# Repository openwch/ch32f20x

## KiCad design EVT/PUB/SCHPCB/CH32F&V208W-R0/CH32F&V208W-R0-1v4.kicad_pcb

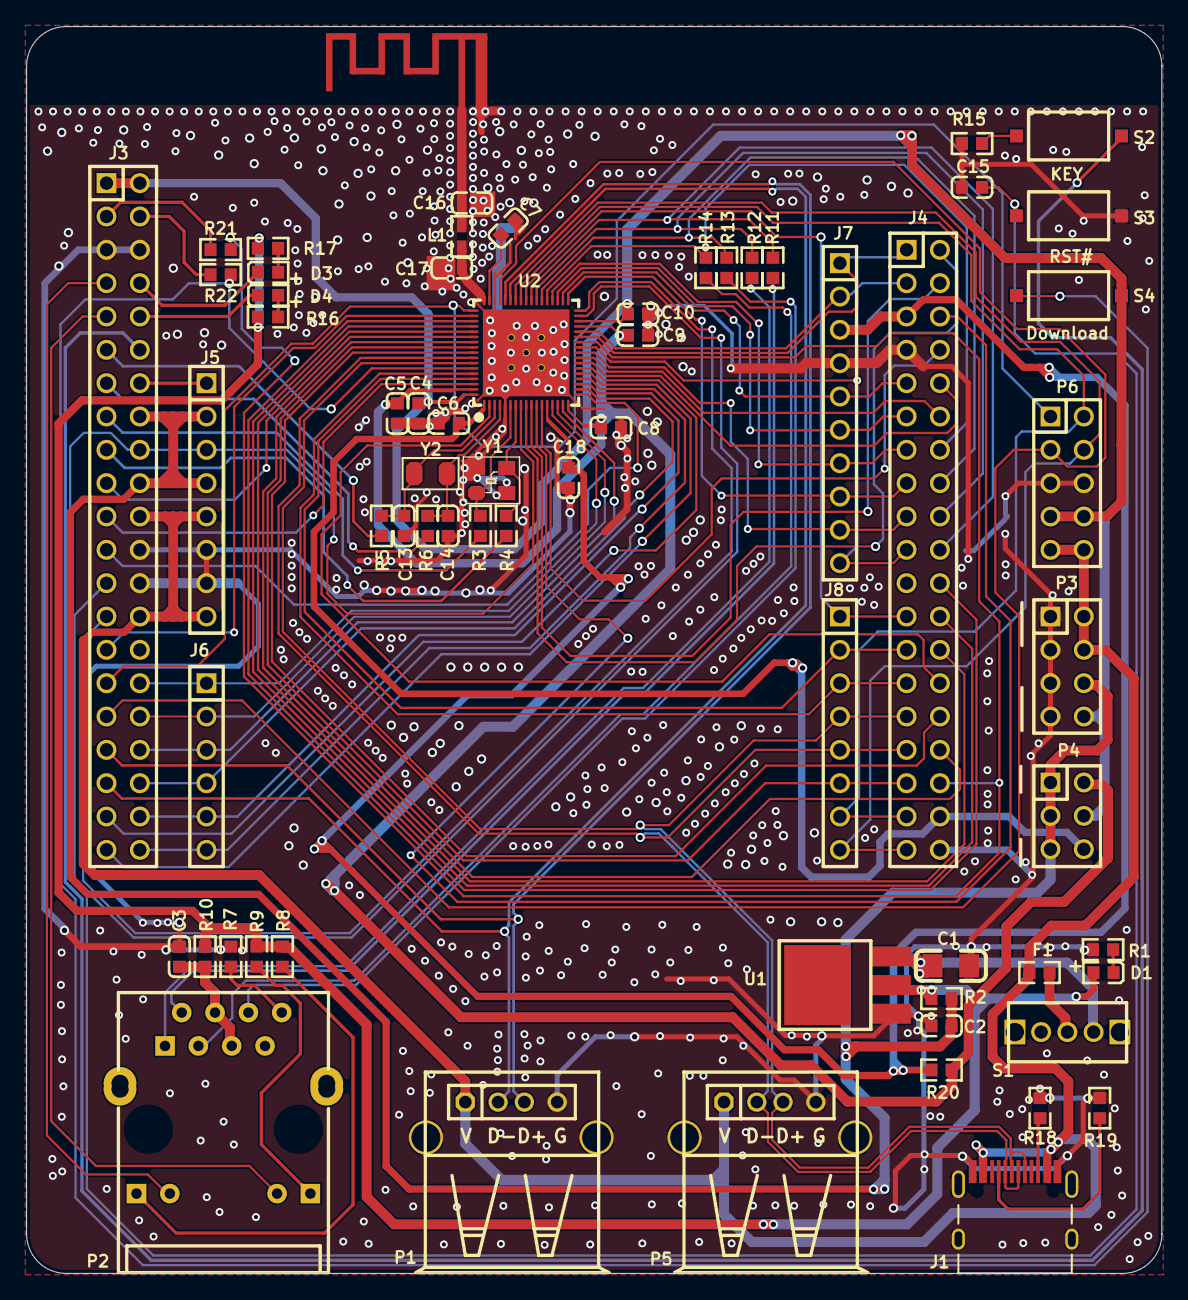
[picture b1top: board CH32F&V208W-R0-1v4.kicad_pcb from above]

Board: 2 copper layers, 86.5 x 95.0 mm, 65 parts (0 on the bottom side), 96 nets.

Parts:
C1: 10uF; 3216_C
C2: 10uF; 0603_C
C3, C4, C5, C6, C8, C9, C10, C15, C18: 0.1uF; 0603_C
C7: 1uF; 0603_C
C13, C14: 12pF; 0603_C
C16: 1.5pF; 0603_C
C17: 1pF; 0603_C
D1: power; 0603+
D3, D4: RED; 0603+
E1: ANTENNA; ANT-F-1-2.4G-1.6
F1: 500mA; 0603
J1: TYPE-C-Receptacle-2.0
J3: Header 21X2; IDC42-2.54mm
J4: Header 19X2; IDC38-2.54mm
J5, J8: Header 8; SIP8-2.54mm
J6: Header 6; SIP6-2.54MM
J7: Header 10; SIP10-2.54mm
L1: 1.8nH; 0603
P1, P5: USB; USBAF
P2: HR911105A
P3: HEADER 4x2; IDC8-2.54mm
P4: Psel; IDC6-2.54mm
P6: LINK; IDC10-2.54mm
R1, R8, R9, R16, R17: 1K; 0603
R2, R7, R10, R20: 0Ω; 0603
R3, R4, R5, R6, R11, R12, R13, R14: NC(0R); 0603
R15, R21, R22: 10K; 0603
R18, R19: NC(5.1K); 0603
S1: SW SPDT; KEY_B
S2: KEY; SMD_6.1x3.65x2.5mm-KEY
S3: RST#; SMD_6.1x3.65x2.5mm-KEY
S4: Download; SMD_6.1x3.65x2.5mm-KEY
U1: 1117-3.3V; SOT-223
U2: CH32F208W; QFN68_8x8
Y1: 32MHz; XT3225
Y2: 32768Hz; FC-135

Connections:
3V3: C2.1, J3.16, J3.20, J5.2, J5.4, P3.6, P4.1, P4.3, P4.5, R2.1
3V3S: D1.1, R2.2, R8.1, R9.1, R10.2, R16.1, R17.1, U1.2
+5V: F1.1, J1.A4, J1.B4, J3.22, J3.28, J5.5, J5.8, P1.1, P3.2, P3.4, P5.1, P6.9, P6.10
ANT: C17.2, L1.1, U2.51
BOOT0: R22.2, S4.2, U2.63
BOOT1: J4.34, R21.1, U2.28
CC1: J1.A5, R19.1
CC2: J1.B5, R18.1
ELED1: J3.7, P2.10
ELED2: J3.9, P2.11
ERXN: P2.6, R13.2
ERXP: P2.3, R14.2
ETXN: P2.2, R11.2
ETXP: P2.1, R12.2
GND: C1.2, C2.2, C3.1, C4.2, C5.1, C6.2, C7.2, C8.2, C9.2, C10.1, C13.1, C14.1, C15.1, C16.1, C17.1, C18.2, E1.0, J1.0, J1.A1, J1.B1, J3.5, J3.6, J3.24, J3.26, J4.7, J4.38, J5.6, J5.7, J7.4, P1.0, P1.4, P3.1, P3.3, P3.5, P3.7, P5.0, P5.4, P6.5, P6.6, R1.1, R7.1, R15.1, R18.2, R19.2, S3.1, U1.1, U2.0, U2.5, U2.49, Y1.2, Y1.4
KEY: J3.12, S2.1
LED1: D3.2, J3.8
LED2: D4.2, J3.10
NRST: C15.2, J3.18, J5.3, S3.2, U2.8
NetC3_2: C3.2, P2.4, P2.5, R10.1
NetC16_2: C16.2, E1.1, L1.2
NetD1_2: D1.2, R1.2
NetD3_1: D3.1, R17.2
NetD4_1: D4.1, R16.2
NetF1_2: F1.2, S1.1
NetJ3_3: J3.3, R21.2
NetJ3_4: J3.4, R22.1
NetJ3_14: J3.14, J5.1
NetP2_8: P2.8, R7.2
NetP2_9: P2.9, R8.2
NetP2_12: P2.12, R9.2
NetR15_2: R15.2, S2.2
PA0: J3.32, J6.1, U2.14
PA1: J3.34, J6.2, U2.15
PA2: J3.36, J6.3, U2.16
PA3: J3.38, J6.4, U2.19
PA4: J3.40, J6.5, U2.20
PA5: J3.42, J6.6, U2.21
PA6: J3.41, U2.22
PA7: J3.39, U2.23
PA8: J4.23, J8.1, U2.43
PA9: J4.35, J8.7, P6.2, U2.44
PA10: J4.37, J8.8, P6.4, U2.45
PA11: J3.37, P1.2, U2.46
PA12: J3.35, P1.3, U2.47
PA13: J3.33, P6.3, U2.48
PA14: J3.31, P6.1, U2.52
PA15: J3.29, U2.53
PB0: J4.17, J7.9, U2.26
PB1: J4.19, J7.10, U2.27
PB3: J4.32, U2.58
PB4: J4.33, J8.6, U2.59
PB5: J4.30, U2.60
PB6: J1.A7, J1.B7, J4.31, J8.5, P5.2, U2.61
PB7: J1.A6, J1.B6, J4.29, J8.4, P5.3, U2.62
PB8: J4.27, J8.3, U2.64
PB9: J4.25, J8.2, U2.65
PB10: J4.1, J7.1, U2.29
PB11: J4.3, J7.2, U2.30
PB12: J4.15, J7.8, U2.35
PB13: J4.9, J7.5, U2.36
PB14: J4.11, J7.6, U2.37
PB15: J4.13, J7.7, U2.38
PC0: J4.2, U2.9
PC1: J4.4, U2.10
PC2: J4.6, U2.11
PC3: J4.8, U2.12
PC4: J4.10, U2.24
PC5: J4.12, U2.25
PC6: J4.14, R14.1, U2.39
PC7: J4.16, R13.1, U2.40
PC8: J4.18, R12.1, U2.41
PC9: J4.20, R11.1, U2.42
PC10: J4.22, U2.54
PC11: J4.24, U2.55
PC12: J4.26, U2.56
PC13: J4.28, U2.2
PC14: J3.11, R5.1
PC15: J3.13, R6.1
PD0: J3.15, R3.1
PD1: J3.17, R4.1
PD2: J3.19, U2.57
PD3: J3.21, U2.66
PD4: J3.23, U2.18
PD5: J3.25, U2.33
PD6: J3.27, U2.34
V5V: C1.1, S1.2, U1.3
VBAT: C6.1, J4.36, P4.6, U2.1
VDD: C4.1, C10.2, J3.1, J3.2, P3.8, P4.4, P6.7, P6.8, S4.1, U2.32, U2.68
VDDA: C18.1, J4.5, J7.3, R20.2, U2.13
VINTA: C7.1, U2.50
VIO: C5.2, C8.1, C9.1, P4.2, R20.1, U2.17, U2.31, U2.67
X32IN: C13.2, R5.2, U2.3, Y2.1
X32OUT: C14.2, R6.2, U2.4, Y2.2
XIN: R3.2, U2.6, Y1.1
XOUT: R4.2, U2.7, Y1.3

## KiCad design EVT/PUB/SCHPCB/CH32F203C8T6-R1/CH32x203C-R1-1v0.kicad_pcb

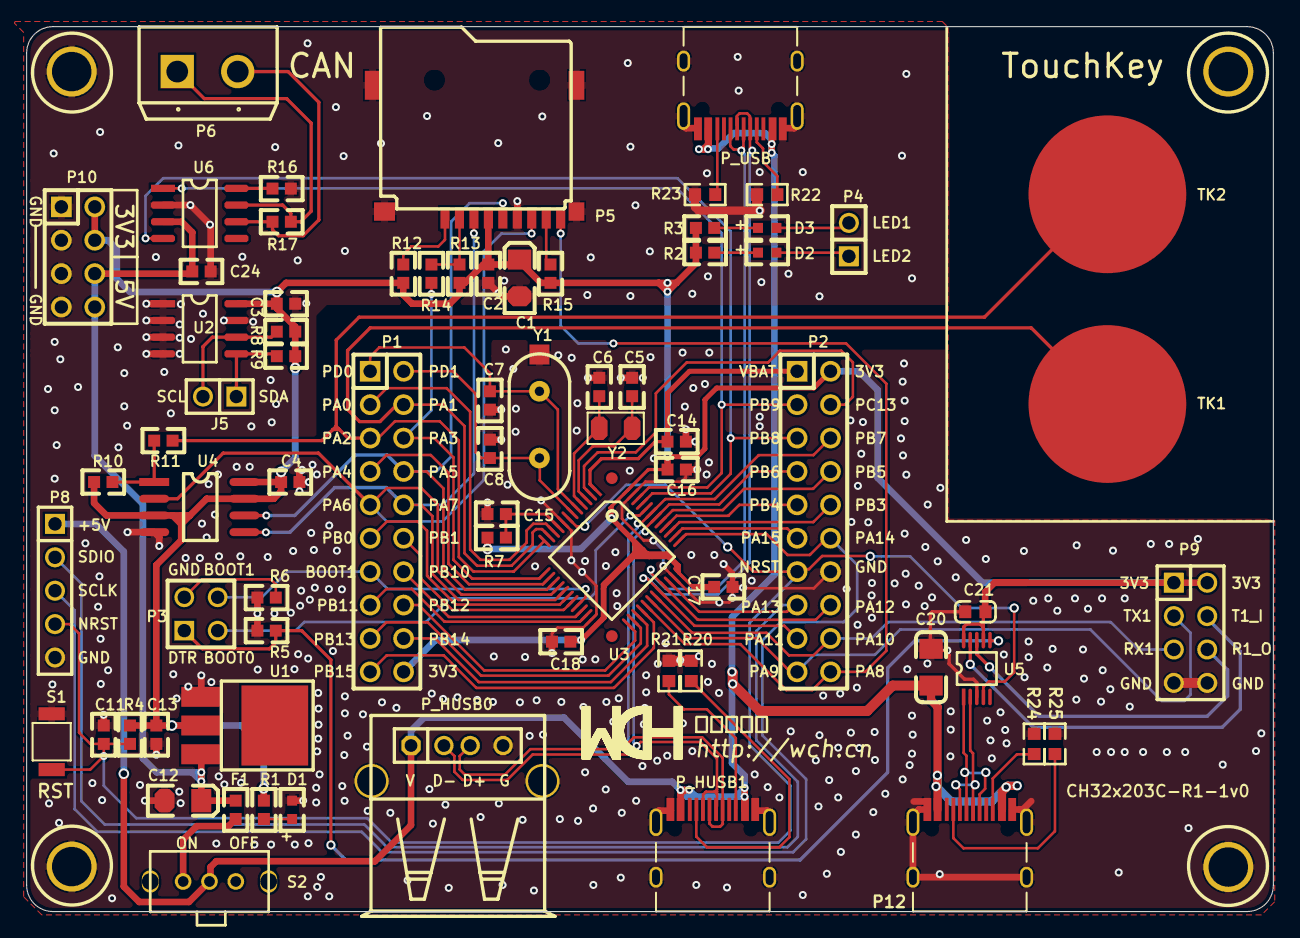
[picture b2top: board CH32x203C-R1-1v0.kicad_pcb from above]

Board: 2 copper layers, 94.8 x 67.3 mm, 72 parts (0 on the bottom side), 72 nets.

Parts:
C1: NC(10uF); 3216
C2, C4, C11, C14, C15, C16, C17, C18: 0.1uF; 0603
C3, C24: NC(0.1uF); 0603
C5, C6: 12pF; 0603
C7, C8: 22pF; 0603
C12: 10uF; 3216
C13: 10uF; 0603
C20: NC(10uF); 3216_C
C21: NC(0.1uF); 0603_C
D1: POWER; 0603L
D2: LED1 blue; 0603L
D3: LED2 blue; 0603L
F1: 500mA; 0603
J5: Header 2; SIP2 - 40mil
P1, P2: Header 10X2; IDC20
P3: Header 2X2; HDR2X2
P4: Header 2; SIP2 - 40mil
P5: TF_自弹; TF_CARD
P6: Header 2; PORT2 4.5MM
P8: Header 5; SIP5 - 40mil
P9: HEADER 4x2; IDC8-2.54mm
P10: Header 4X2; IDC8
P12: TYPE-C; TYPE-C-Receptacle-2.0
P_HUSB0: USB_A; USBA-l
P_HUSB1: TYPE-C; TYPE-C-Receptacle-2.0
P_USB: TYPE-C; TYPE-C-Receptacle-2.0
R1, R2, R3: 1K; 0603
R4, R5, R6, R10: 10K; 0603
R7: 0Ω; 0603
R8, R9, R12, R13, R15: NC(10K); 0603
R11, R14, R16: NC(0Ω); 0603
R17: NC(120Ω); 0603
R20, R21, R22, R23, R24, R25: NC(5.1K); 0603
S1: KEY; 贴片按键
S2: SW; KEY2
TK1: KEY6; KEY68
TK2: KEY7; KEY68
U1: 1117_3V3; SOT-223
U2: NC(24C02); SOP8
U3: CH32F203CxT; LQFP48
U4: W25Q16; 016 SO-8
U5: NC(CH340X); MSOP10
U6: NC(TJA1050); SOP8
Y1: 8M; 28
Y2: 32.768k; FC-135

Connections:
3V3: C1.1, C2.1, C3.2, C4.2, C13.1, C16.2, C17.2, C18.2, C21.1, P1.20, P2.2, P5.4, P9.1, P9.2, P10.2, P10.4, R1.2, R2.1, R3.1, R4.2, R7.1, R8.1, R9.1, R10.2, R12.2, R13.2, R15.1, U1.2, U2.8, U3.24, U3.36, U3.48, U4.3, U4.7, U4.8, U5.7, U5.10
5V: C12.1, C24.2, F1.2, P10.6, P10.8, U1.3, U6.3
+5V: C20.2, P8.1, P12.A4, P12.B4, P_HUSB0.1, P_HUSB1.A4, P_HUSB1.B4, P_USB.A4, P_USB.B4, S2.1
BOOT0: P3.3, U3.44
BOOT1: P1.13, P3.4, U3.20
CAN0H: P6.1, R17.1, U6.7
CAN0L: P6.2, R17.2, U6.6
DTR: P3.1, R5.1, U5.6
GND: C1.2, C2.2, C3.1, C4.1, C5.2, C6.2, C7.1, C8.1, C11.1, C12.2, C13.2, C14.2, C15.2, C16.1, C17.1, C18.1, C20.1, C21.2, C24.1, D1.2, P2.14, P5.6, P5.10, P8.5, P9.7, P9.8, P10.1, P10.3, P10.5, P10.7, P12.0, P12.A1, P12.B1, P_HUSB0.4, P_HUSB0.5, P_HUSB0.6, P_HUSB1.0, P_HUSB1.A1, P_HUSB1.B1, P_USB.0, P_USB.A1, P_USB.B1, R5.2, R6.2, R16.1, R20.2, R21.2, R22.2, R23.2, R24.2, R25.2, S1.3, U1.1, U2.1, U2.2, U2.3, U2.4, U2.7, U3.8, U3.23, U3.35, U3.47, U4.4, U5.3, U6.2, Y1.0
IIC_SCL: J5.2, R8.2, U2.6
IIC_SDA: J5.1, R9.2, U2.5
LED1: D2.2, P4.1
LED2: D3.2, P4.2
MCU_RXD: P9.6, U5.8
MCU_TXD: P9.4, U5.9
NRST: C11.2, P2.13, P8.4, R4.1, S1.1, U3.7, U5.4
NetD1_1: D1.1, R1.1
NetD2_1: D2.1, R2.2
NetD3_1: D3.1, R3.2
NetF1_1: F1.1, S2.2
NetP3_2: P3.2, R6.1
NetP5_1: P5.1, R12.1
NetP5_2: P5.2, R13.1, R14.1
NetP5_8: P5.8, R15.2
NetP12_A5: P12.A5, R25.1
NetP12_B5: P12.B5, R24.1
NetP_HUSB1_A5: P_HUSB1.A5, R20.1
NetP_HUSB1_B5: P_HUSB1.B5, R21.1
NetP_USB_A5: P_USB.A5, R22.1
NetP_USB_B5: P_USB.B5, R23.1
NetR10_1: R10.1, R11.1, U4.1
NetR16_2: R16.2, U6.8
PA0: P1.3, U3.10
PA1: P1.4, TK1.1, U3.11
PA2: P1.5, R11.2, TK2.1, U3.12
PA3: P1.6, R14.2, U3.13
PA4: P1.7, U3.14
PA5: P1.8, P5.5, U3.15, U4.6
PA6: P1.9, P5.7, U3.16, U4.2
PA7: P1.10, P5.3, U3.17, U4.5
PA8: P2.20, P5.9, U3.29
PA9: P2.19, P9.3, U3.30
PA10: P2.18, P9.5, U3.31
PA11: P2.17, P_USB.A7, P_USB.B7, U3.32
PA12: P2.16, P_USB.A6, P_USB.B6, U3.33
PA13: P2.15, P8.2, U3.34
PA14: P2.12, P8.3, U3.37
PA15: P2.11, U3.38
PB0: P1.11, U3.18
PB1: P1.12, U3.19
PB3: P2.10, U3.39
PB4: P2.9, U3.40
PB5: P2.8, U3.41
PB6: P2.7, P_HUSB0.2, P_HUSB1.A7, P_HUSB1.B7, U3.42
PB7: P2.6, P_HUSB0.3, P_HUSB1.A6, P_HUSB1.B6, U3.43
PB8: P2.5, U3.45, U6.4
PB9: P2.3, U3.46, U6.1
PB10: P1.14, U3.21
PB11: P1.15, U3.22
PB12: P1.16, U3.25
PB13: P1.17, U3.26
PB14: P1.18, U3.27
PB15: P1.19, U3.28
PC13: P2.4, U3.2
PC14: C5.1, U3.3, Y2.1
PC15: C6.1, U3.4, Y2.2
PD0: C7.2, P1.1, U3.5, Y1.2
PD1: C8.2, P1.2, U3.6, Y1.1
UD+: P12.A6, P12.B6, U5.1
UD-: P12.A7, P12.B7, U5.2
VBAT: C14.1, P2.1, U3.1
VDDA: C15.1, R7.2, U3.9

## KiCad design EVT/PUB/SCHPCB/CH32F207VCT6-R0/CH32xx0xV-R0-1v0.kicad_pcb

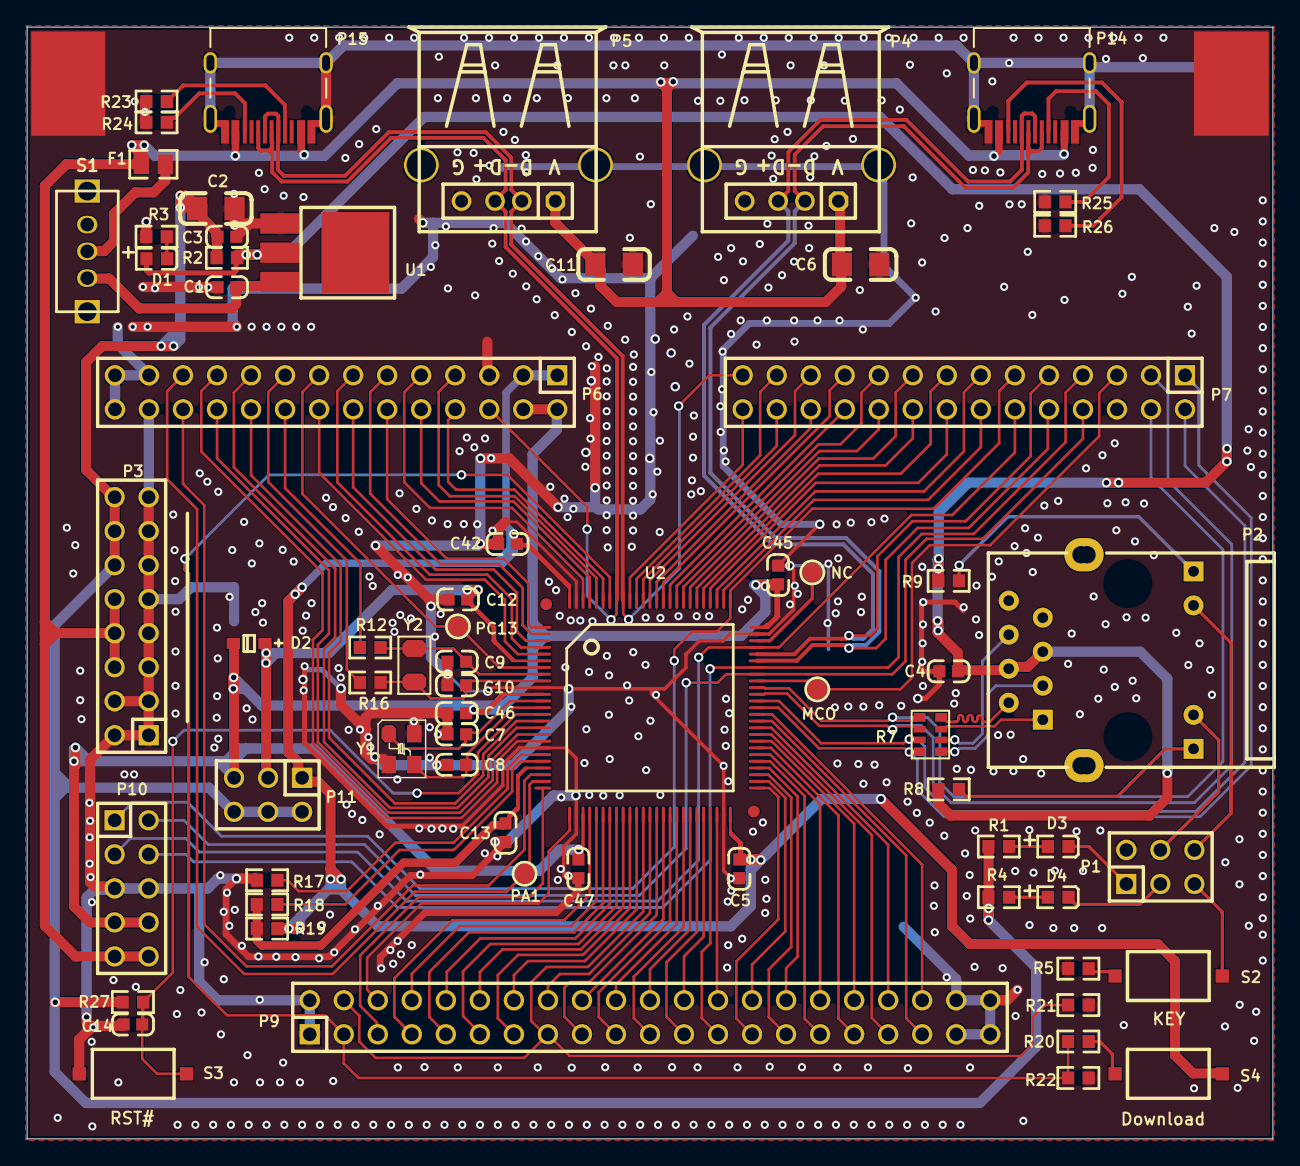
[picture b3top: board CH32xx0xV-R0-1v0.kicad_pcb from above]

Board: 2 copper layers, 93.0 x 83.0 mm, 68 parts (0 on the bottom side), 119 nets.

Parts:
C1, C3, C4, C5, C12, C13, C14, C42, C45, C46, C47: 0.1uF; 0603_C
C2, C6, C11: 10uF; 3216_C
C7, C8: 22pF; 0603_C
C9, C10: 12pF; 0603_C
D1, D4: RED; 0603+
D2: B0520WS; SOD-323
D3: BLUE; 0603+
F1: 500mA; 0805
MCO: Testpoint; TESTPOINT1
NC: Testpoint; TESTPOINT1
P1: IO; IDC6-2.54mm
P2: HR911105A
P3: HEADER 8x2; IDC16-2.54mm
P4: USBFS; USBAF
P5: USBHS; USBAF
P6, P7: HEADER 14x2; IDC28-2.54MM
P9: HEADER 21x2; IDC42-2.54MM
P10: LINK; IDC10-2.54mm
P11: HEADER 3x2; IDC6-2.54mm
P14: USBFS; TYPE-C-Receptacle-2.0
P15: USBHS; TYPE-C-Receptacle-2.0
PA1: Testpoint; TESTPOINT1
PC13: Testpoint; TESTPOINT1
R1, R3, R4, R8, R9, R20: 1K; 0603
R2, R17, R18, R19: 0R; 0603
R5, R21, R22, R27: 10K; 0603
R7: 0Ω; RCA-8P4R-0603
R12, R16: NC(0R); 0603
R23, R24, R25, R26: 5.1K; 0603
S1: SW SPDT; KEY2
S2: KEY; SMD_6.1x3.65x2.5mm-KEY
S3: RST#; SMD_6.1x3.65x2.5mm-KEY
S4: Download; SMD_6.1x3.65x2.5mm-KEY
U1: 1117-3.3V; SOT-223
U2: CH32F207V; LQFP100
Y1: 8MHz; XT3225
Y2: 32768Hz; FC-135

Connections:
3V3: C2.1, C3.1, P3.12, P3.14, P3.16, P11.2, P11.4, P11.6, R1.1, R2.1, R4.1, R27.2
3V3S: C4.2, D1.1, P2.4, P2.5, R2.2, R8.1, R9.1, U1.2
5V: C6.1, C11.1, F1.1, P3.6, P3.8, P3.10, P4.1, P5.1, P10.9, P10.10, P14.A4, P14.B4, P15.A4, P15.B4
BOOT0: P9.3, R20.1, R22.1, U2.94
BOOT1: P9.4, P9.15, R21.1, U2.37
ELED1: P1.4, P2.10
ELED2: P1.6, P2.11
ERXN: P7.2, R7.3, U2.64
ERXN1: P2.6, R7.6
ERXP: P7.1, R7.4, U2.63
ERXP1: P2.3, R7.5
ETXN: P7.4, R7.1, U2.66
ETXN1: P2.2, R7.8
ETXP: P7.3, R7.2, U2.65
ETXP1: P2.1, R7.7
GND: C1.2, C2.2, C3.2, C4.1, C5.2, C6.2, C7.1, C8.1, C9.1, C10.1, C11.2, C12.1, C13.2, C14.1, C42.1, C45.2, C46.2, C47.1, P1.2, P2.8, P3.1, P3.2, P3.3, P3.4, P3.5, P3.7, P3.9, P3.11, P3.13, P3.15, P4.0, P4.4, P5.0, P5.4, P6.5, P6.25, P6.26, P6.27, P6.28, P7.6, P9.1, P9.2, P9.39, P9.40, P9.41, P9.42, P10.5, P10.6, P14.0, P14.A1, P14.B1, P15.0, P15.A1, P15.B1, R3.2, R5.1, R17.1, R21.2, R22.2, R23.2, R24.2, R25.2, R26.2, S3.1, U1.1, U2.10, U2.19, U2.27, U2.49, U2.74, U2.99, Y1.2, Y1.4
KEY: P1.5, S2.1
LED1: D3.2, P1.1
LED2: D4.2, P1.3
MCO: MCO.1, P7.5, U2.67
NC: NC.1, U2.73
NRST: C14.2, R27.1, S3.2, U2.14
NetC1_1: C1.1, S1.2, U1.3
NetD1_2: D1.2, R3.1
NetD3_1: D3.1, R1.2
NetD4_1: D4.1, R4.2
NetF1_2: F1.2, S1.1
NetP2_9: P2.9, R8.2
NetP2_12: P2.12, R9.2
NetP14_A5: P14.A5, R25.1
NetP14_B5: P14.B5, R26.1
NetP15_A5: P15.A5, R23.1
NetP15_B5: P15.B5, R24.1
NetR5_2: R5.2, S2.2
NetR20_2: R20.2, S4.2
PA0: P6.24, U2.23
PA1: P6.23, PA1.1, U2.24
PA2: P9.5, U2.25
PA3: P9.6, U2.26
PA4: P9.7, U2.29
PA5: P9.8, U2.30
PA6: P9.9, U2.31
PA7: P9.10, U2.32
PA9: P7.8, P10.2, U2.68
PA10: P7.7, P10.4, U2.69
PA11: P4.2, P7.10, P14.A7, P14.B7, U2.70
PA12: P4.3, P7.9, P14.A6, P14.B6, U2.71
PA13: P7.12, P10.3, U2.72
PA14: P7.11, P10.1, U2.76
PA15: P7.14, U2.77
PB0: P9.13, U2.35
PB1: P9.14, U2.36
PB3: P7.26, U2.89
PB4: P7.25, U2.90
PB5: P7.28, U2.91
PB6: P5.2, P7.27, P15.A7, P15.B7, U2.92
PB7: P5.3, P6.6, P15.A6, P15.B6, U2.93
PB8: P6.8, U2.95
PB9: P6.7, U2.96
PB10: P9.25, U2.47
PB11: P9.26, U2.48
PB12: P9.27, U2.51
PB13: P9.28, U2.52
PB14: P9.29, U2.53
PB15: P9.30, U2.54
PC0: P6.20, U2.15
PC1: P6.19, U2.16
PC2: P6.22, U2.17
PC3: P6.21, U2.18
PC4: P9.11, U2.33
PC5: P9.12, U2.34
PC10: P7.13, U2.78
PC11: P7.16, U2.79
PC12: P7.15, U2.80
PC13: P6.15, PC13.1, U2.7
PC14: P6.18, R12.1
PC15: P6.17, R16.1
PD0: P7.18, U2.81
PD1: P7.17, U2.82
PD2: P7.20, U2.83
PD3: P7.19, U2.84
PD4: P7.22, U2.85
PD5: P7.21, U2.86
PD6: P7.24, U2.87
PD7: P7.23, U2.88
PD8: P9.31, U2.55
PD9: P9.32, U2.56
PD10: P9.33, U2.57
PD11: P9.34, U2.58
PD12: P9.35, U2.59
PD13: P9.36, U2.60
PD14: P9.37, U2.61
PD15: P9.38, U2.62
PE0: P6.10, U2.97
PE1: P6.9, U2.98
PE2: P6.12, U2.1
PE3: P6.11, U2.2
PE4: P6.14, U2.3
PE5: P6.13, U2.4
PE6: P6.16, U2.5
PE7: P9.16, U2.38
PE8: P9.17, U2.39
PE9: P9.18, U2.40
PE10: P9.19, U2.41
PE11: P9.20, U2.42
PE12: P9.21, U2.43
PE13: P9.22, U2.44
PE14: P9.23, U2.45
PE15: P9.24, U2.46
VBAT: C12.2, D2.1, P11.3, U2.6
VDD: C45.1, C46.1, C47.2, D2.2, P6.2, P6.4, P10.7, P10.8, P11.5, U2.11, U2.28, U2.75
VDDA: C13.1, R18.1, R19.2, U2.22
VIO: C5.1, C42.2, P6.1, P6.3, P11.1, R19.1, S4.1, U2.50, U2.100
VREF+: R18.2, U2.21
VREF-: R17.2, U2.20
X32KI: C9.2, R12.2, U2.8, Y2.1
X32KO: C10.2, R16.2, U2.9, Y2.2
XI: C7.2, U2.12, Y1.1
XO: C8.2, U2.13, Y1.3

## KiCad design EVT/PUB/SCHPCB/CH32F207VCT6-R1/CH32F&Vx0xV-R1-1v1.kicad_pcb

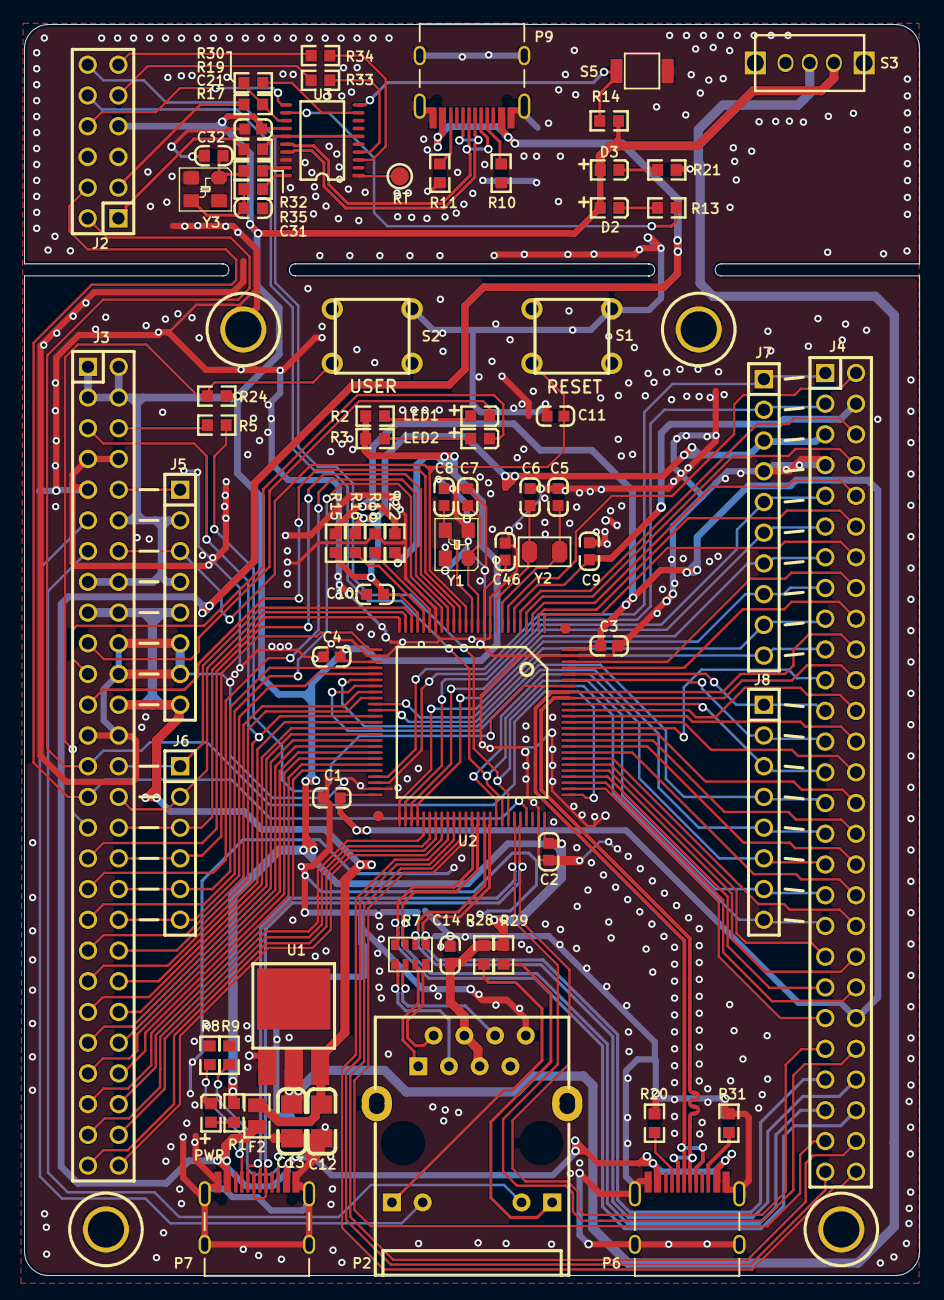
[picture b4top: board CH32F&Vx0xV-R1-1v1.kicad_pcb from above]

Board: 2 copper layers, 74.0 x 103.4 mm, 74 parts (0 on the bottom side), 137 nets.

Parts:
C1, C2, C3, C4, C9, C10, C11, C14, C21, C46: 0.1uF; 0603_C
C5, C6: 12pF; 0603_C
C7, C8: 22pF; 0603_C
C12, C13: 10uF; 3216_C
C31, C32: NC(22pF); 0603_C
D2: BLUE; 0603+
D3: RED; 0603+
F2: 500mA; 0805
J2: Header 6X2; IDC12-2.54mm
J3, J4: HEADER 27x2; IDC54-2.54MM
J5, J8: Header 8; SIP8-2.54mm
J6: Header 6; SIP6-2.54MM
J7: Header 10; SIP10-2.54mm
LED1: LED1 blue; 0603+
LED2: LED2 blue; 0603+
P2: HR911105A
P6: USBHS; TYPE-C-Receptacle-2.0
P7: USBFS; TYPE-C-Receptacle-2.0
P9: TYPE-C; TYPE-C-Receptacle-2.0
PWR: POWER red; 0603+
R1, R2, R3, R13, R21, R28, R29, R30: 1K; 0603
R5, R14, R24: 10K; 0603
R7: 0Ω; RCA-8P4R-0603
R8, R9, R10, R11, R20, R31: NC(5.1K); 0603
R15, R16, R18, R22: 0Ω; 0603
R17, R19: 100; 0603
R32, R35: NC(0R); 0603
R33, R34: 270; 0603
RT: Testpoint; TESTPOINT1
S1: RESET; KEYX
S2: USER; KEYX
S3: SW; SW1
S5: KEY; 贴片按键
U1: 1117-3.3V; SOT-223
U2: CH32F207V; LQFP100
U3: CH32V305F; TSSOP20
Y1: 8M; XT3225
Y2: 32.768k; FC-135
Y3: NC(12M); XT3225

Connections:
5V_in: F2.1, P6.A4, P6.B4, P7.A4, P7.B4, P9.A4, P9.B4
+5V: C12.1, F2.2, J3.17, J3.18, J3.24, J5.5, J5.8, U1.3
BOOT0: R5.2, U2.94
BOOT1: J3.5, J3.41, U2.37
CLK: J2.2, J3.27, U2.76
CLK0: J2.1, R17.1
DIO: J2.4, J3.29, U2.72
DIO0: J2.3, R19.1
D_SWCLK: R17.2, U3.6, U3.15
D_SWDIO: R19.2, R30.1, U3.13
ELED1: J3.11, P2.10
ELED2: J3.13, P2.11
ERXN: J4.49, R7.3, U2.64
ERXN1: P2.6, R7.6
ERXP: J4.50, R7.4, U2.63
ERXP1: P2.3, R7.5
ETXN: J4.47, R7.1, U2.66
ETXN1: P2.2, R7.8
ETXP: J4.48, R7.2, U2.65
ETXP1: P2.1, R7.7
GND: C1.1, C2.1, C3.2, C4.1, C5.2, C6.2, C7.1, C8.1, C9.1, C10.1, C11.1, C12.2, C13.2, C14.1, C21.2, C31.1, C32.1, C46.2, J2.5, J2.6, J3.7, J3.8, J3.9, J3.20, J3.22, J3.25, J3.26, J4.7, J5.6, J5.7, J7.4, P2.8, P6.0, P6.A1, P6.B1, P7.0, P7.A1, P7.B1, P9.0, P9.A1, P9.B1, PWR.2, R8.1, R9.1, R10.2, R11.2, R18.1, R20.1, R21.1, R31.1, S1.3, S2.3, S5.2, U1.1, U2.10, U2.19, U2.27, U2.49, U2.74, U2.99, U3.18, Y1.2, Y1.4, Y3.2, Y3.4
IAP: R14.1, S5.1, U3.10
KEY: J3.31, R24.1, S2.1
LED1: J3.19, LED1.2
LED2: J3.21, LED2.2
LED_CON: R13.1, U3.12
NRST: C11.2, J3.14, J5.3, S1.1, U2.14
NetC13_1: C13.1, S3.1, U1.2
NetD2_2: D2.2, R13.2
NetD3_2: D3.2, R21.2
NetJ3_6: J3.6, R5.1
NetJ3_10: J3.10, J5.1
NetLED1_1: LED1.1, R2.2
NetLED2_1: LED2.1, R3.2
NetP2_9: P2.9, R28.2
NetP2_12: P2.12, R29.2
NetP6_A5: P6.A5, R20.2
NetP6_B5: P6.B5, R31.2
NetP7_A5: P7.A5, R8.2
NetP7_B5: P7.B5, R9.2
NetP9_A5: P9.A5, R10.1
NetP9_B5: P9.B5, R11.1
NetPWR_1: PWR.1, R1.1
OSC_IN: C32.2, R32.2, Y3.1
OSC_OUT: C31.2, R35.2, Y3.3
PA0: J3.28, J6.1, U2.23
PA1: J3.30, J6.2, U2.24
PA2: J3.32, J6.3, U2.25
PA3: J3.34, J6.4, U2.26
PA4: J3.36, J6.5, U2.29
PA5: J3.38, J6.6, U2.30
PA6: J4.29, J8.4, U2.31
PA7: J4.31, J8.5, U2.32
PA8: J4.33, J8.6, U2.67
PA9: J2.10, J4.35, J8.7, U2.68
PA10: J2.12, J4.37, J8.8, U2.69
PA11: J4.46, P7.A7, P7.B7, U2.70
PA12: J4.45, P7.A6, P7.B6, U2.71
PA15: J4.43, U2.77
PB0: J4.17, J7.9, U2.35
PB1: J4.19, J7.10, U2.36
PB3: J4.26, U2.89
PB4: J4.24, U2.90
PB5: J4.27, J8.3, U2.91
PB6: J4.22, P6.A7, P6.B7, U2.92
PB7: J4.20, P6.A6, P6.B6, U2.93
PB8: J4.25, J8.2, U2.95
PB9: J4.23, J8.1, U2.96
PB10: J4.1, J7.1, U2.47
PB11: J4.3, J7.2, U2.48
PB12: J4.15, J7.8, U2.51
PB13: J4.9, J7.5, U2.52
PB14: J4.11, J7.6, U2.53
PB15: J4.13, J7.7, U2.54
PC0: J3.23, U2.15
PC1: J3.33, U2.16
PC2: J3.35, U2.17
PC3: J3.37, U2.18
PC4: J3.39, U2.33
PC5: J3.40, U2.34
PC6_305: R30.2, U3.9
PC10: J4.42, U2.78
PC11: J4.41, U2.79
PC12: J4.40, U2.80
PC13: J4.2, U2.7
PC14: C5.1, U2.8, Y2.1
PC15: C6.1, U2.9, Y2.2
PD0: J4.39, U2.81
PD0_305: R32.1, U3.19
PD1: J4.38, U2.82
PD1_305: R35.1, U3.20
PD2: J4.36, U2.83
PD3: J4.34, U2.84
PD4: J4.32, U2.85
PD5: J4.30, U2.86
PD6: J4.21, U2.87
PD7: J4.28, U2.88
PD8: J3.51, U2.55
PD9: J3.52, U2.56
PD10: J3.53, U2.57
PD11: J3.54, U2.58
PD12: J4.54, U2.59
PD13: J4.53, U2.60
PD14: J4.52, U2.61
PD15: J4.51, U2.62
PE0: J4.18, U2.97
PE1: J4.16, U2.98
PE2: J4.14, U2.1
PE3: J4.12, U2.2
PE4: J4.10, U2.3
PE5: J4.8, U2.4
PE6: J4.6, U2.5
PE7: J3.42, U2.38
PE8: J3.43, U2.39
PE9: J3.44, U2.40
PE10: J3.45, U2.41
PE11: J3.46, U2.42
PE12: J3.47, U2.43
PE13: J3.48, U2.44
PE14: J3.49, U2.45
PE15: J3.50, U2.46
RST0: J2.8, U3.11
RT: RT.1, U3.1
RX_OUT: J2.9, R33.1
TX_OUT: J2.11, R34.1
UART3_RX: R33.2, U3.4
UART3_TX: R34.2, U3.3
USB_N: P9.A7, P9.B7, U3.16
USB_P: P9.A6, P9.B6, U3.17
VBAT: C9.2, J4.4, U2.6
VCC: C2.2, C4.2, C14.2, C21.1, C46.1, D2.1, D3.1, J2.7, J3.1, J3.2, J3.3, J3.4, J3.12, J3.15, J3.16, J5.2, J5.4, P2.4, P2.5, R1.2, R2.1, R3.1, R14.2, R22.2, R24.2, R28.1, R29.1, S3.3, U2.11, U2.28, U2.75, U3.14
VDDA: C10.2, J4.5, J7.3, R15.2, R16.1, U2.22
VIO: C1.2, C3.1, J4.44, R15.1, R22.1, U2.50, U2.100
VREF+: R16.2, U2.21
VREF-: R18.2, U2.20
XI: C7.2, U2.12, Y1.1
XO: C8.2, U2.13, Y1.3
